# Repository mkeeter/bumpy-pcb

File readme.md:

## About

This repository contains hardware for the [bumpy](http://mattkeeter.com/projects/bumpy)
mp3 player.

## License

Copyright (c) 2014 Matthew Keeter

Permission is hereby granted, free of charge, to any person obtaining a copy of this hardware, software, and associated documentation files (the "Product"), to deal in the Product without restriction, including without limitation the rights to use, copy, modify, merge, publish, distribute, sublicense, and/or sell copies of the Product, and to permit persons to whom the Product is furnished to do so, subject to the following conditions:

The above copyright notice and this permission notice shall be included in all copies or substantial portions of the Product.

THE PRODUCT IS PROVIDED "AS IS", WITHOUT WARRANTY OF ANY KIND, EXPRESS OR IMPLIED, INCLUDING BUT NOT LIMITED TO THE WARRANTIES OF MERCHANTABILITY, FITNESS FOR A PARTICULAR PURPOSE AND NONINFRINGEMENT. IN NO EVENT SHALL THE AUTHORS OR COPYRIGHT HOLDERS BE LIABLE FOR ANY CLAIM, DAMAGES OR OTHER LIABILITY, WHETHER IN AN ACTION OF CONTRACT, TORT OR OTHERWISE, ARISING FROM, OUT OF OR IN CONNECTION WITH THE PRODUCT OR THE USE OR OTHER DEALINGS IN THE PRODUCT.

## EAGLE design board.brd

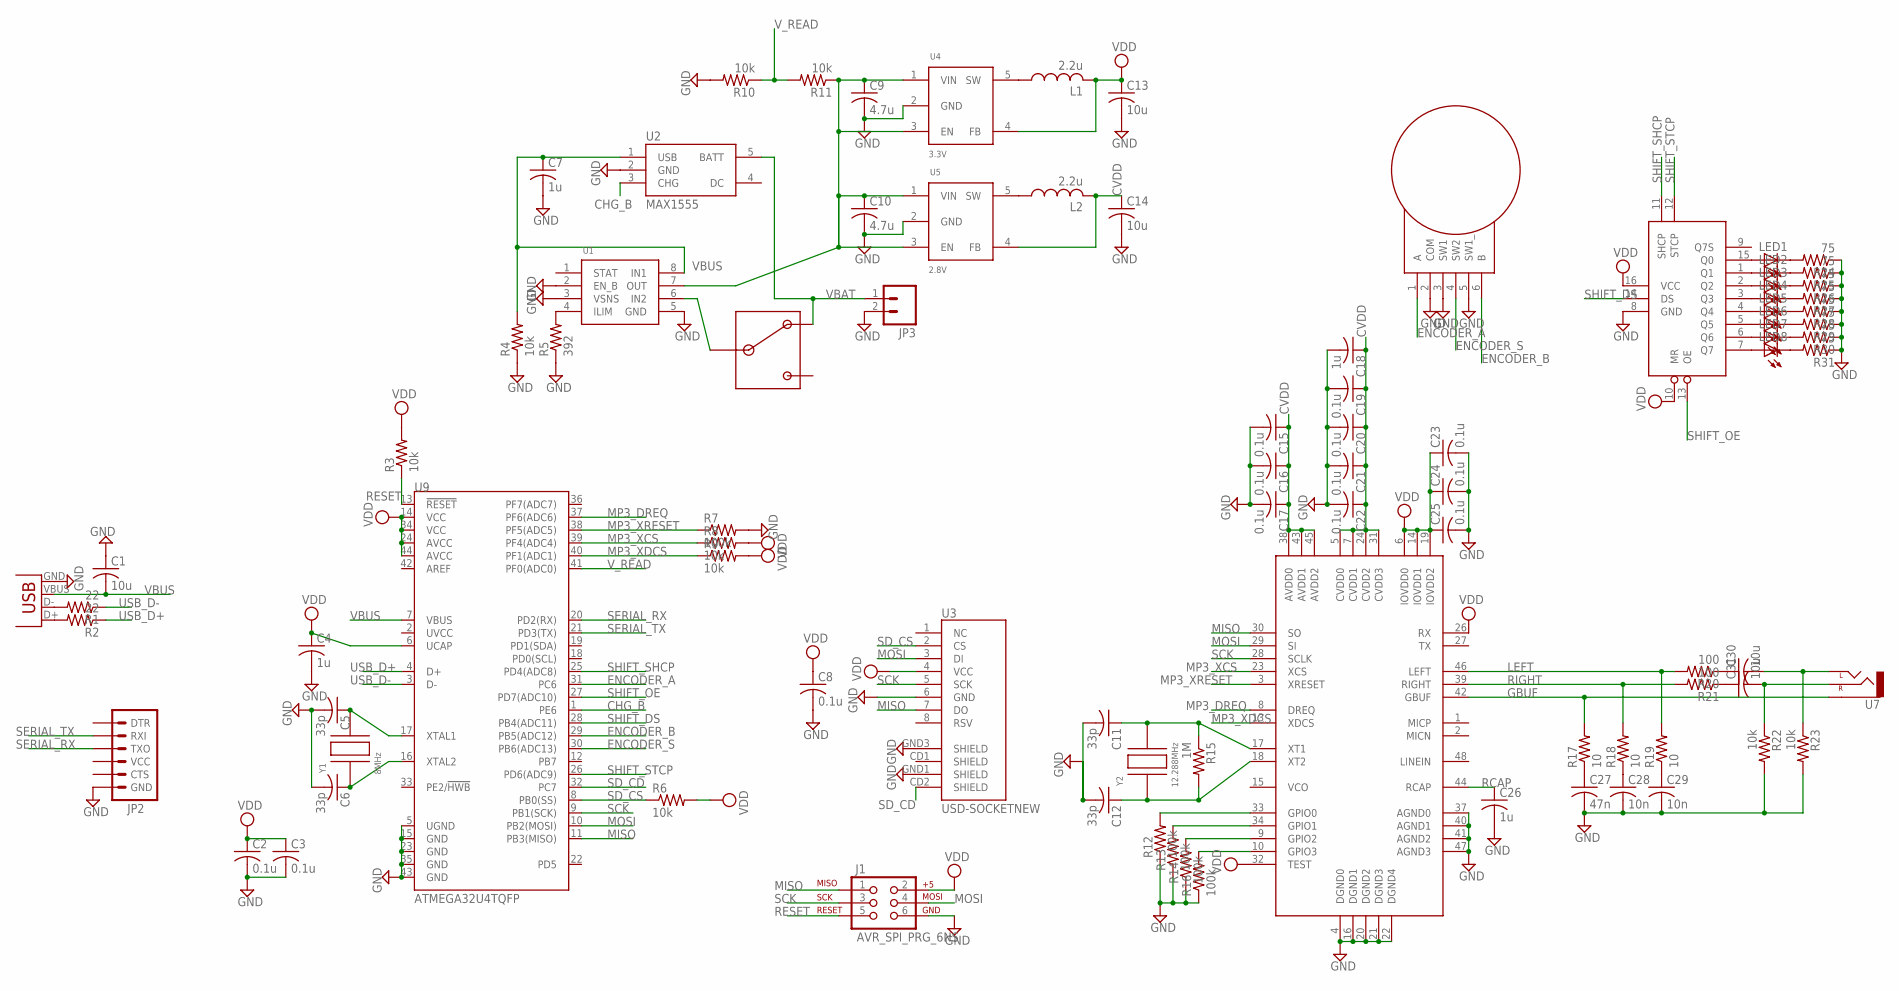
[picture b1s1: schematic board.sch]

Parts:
C1, C13, C14, C30, C31: 10u; C0603K
C2, C3, C8, C15, C16, C17, C19, C20, C21, C22, C23, C24, C25: 0.1u; C0603K
C4, C7, C18, C26: 1u; C0603K
C5, C6, C11, C12: 33p; C0603K
C9, C10: 4.7u; C0603K
C27: 47n; C0603K
C28, C29: 10n; C0603K
J1: AVR_SPI_PRG_6NS; 2X3-NS
JP1: USBSMD; USB-MINIB
JP2: ARDUINO_SERIAL_PROGRAMLOCK; 1X06_LOCK
JP3: M02PTH; 1X02
L1, L2: 2.2u; IHLP-2020CZ-11
LED1, LED2, LED3, LED4, LED5, LED6, LED7, LED8: LED1206; LED-1206
R1, R2: 22; R0603W
R3, R4, R10, R11: 10k; R0603
R5: 392; R0603
R6, R8, R9, R22, R23: 10k; R0603W
R7, R12, R13, R14, R16: 100k; R0603W
R15: 1M; R0603
R17, R18, R19: 10; R0603W
R20, R21: 100; R0603W
R24, R25, R26, R27, R28, R29, R30, R31: 75; R0603W
S1: JS102011SAQN
S2: EVQ-WKA
U1: TPS2112A; TSSOP8
U2: MAX1555; SOT23-5
U3: USD-SOCKETNEW; MICRO-SD-SOCKET-PP
U4: 3.3V; SOT23-5
U5: 2.8V; SOT23-5
U6: 74HC595; TSSOP16
U7: AUDIO-JACKSMD2; AUDIO-JACK-3.5MM-SMD
U8: VS1003; LQFP-48
U9: ATMEGA32U4TQFP; SPARKFUN-DIGITALIC_TQFP44
Y1: 8MHz; HC49/US
Y2: 12.288MHz; CSM-3X

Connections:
CHG_B: U2.3 (CHG), U9.1 (PE6)
CVDD: C14.1, C15.1, C16.1, C17.1, C18.1, C19.1, C20.1, C21.1, C22.1, L2.P$2 (2), U5.4 (FB), U8.5 (CVDD0), U8.7 (CVDD1), U8.24 (CVDD2), U8.31 (CVDD3), U8.38 (AVDD0), U8.43 (AVDD1), U8.45 (AVDD2)
ENCODER_A: S2.1 (A), U9.31 (PC6)
ENCODER_B: S2.6 (B), U9.29 (PB5(ADC12))
ENCODER_S: S2.4 (SW2), U9.30 (PB6(ADC13))
GBUF: R17.2, U7.SLEEVE, U8.42 (GBUF)
GND: C1.1, C2.2, C3.2, C4.2, C5.2, C6.2, C7.2, C8.2, C9.2, C10.2, C11.2, C12.2, C13.2, C14.2, C15.2, C16.2, C17.2, C18.2, C19.2, C20.2, C21.2, C22.2, C23.2, C24.2, C25.2, C26.2, C27.2, C28.2, C29.2, J1.6, JP1.GND, JP2.6 (GND), JP3.2, R4.1, R5.1, R7.2, R10.2, R12.1, R13.1, R14.1, R16.1, R22.2, R23.2, R24.1, R25.1, R26.1, R27.1, R28.1, R29.1, R30.1, R31.1, S2.2 (COM), S2.3 (SW1), S2.5 (SW1_), U1.2 (EN_B), U1.3 (VSNS), U1.5 (GND), U2.2 (GND), U3.6 (GND), U3.GND1 (SHIELD), U3.GND3 (SHIELD), U4.2 (GND), U5.2 (GND), U6.8 (GND), U8.4 (DGND0), U8.16 (DGND1), U8.20 (DGND2), U8.21 (DGND3), U8.22 (DGND4), U8.37 (AGND0), U8.40 (AGND1), U8.41 (AGND2), U8.47 (AGND3), U9.5 (UGND), U9.15 (GND), U9.23 (GND), U9.35 (GND), U9.43 (GND)
GPIO0: R12.2, U8.33 (GPIO0)
GPIO1: R13.2, U8.34 (GPIO1)
GPIO2: R14.2, U8.9 (GPIO2)
GPIO3: R16.2, U8.10 (GPIO3)
LEFT: R19.2, R20.2, U8.46 (LEFT)
MISO: J1.1, U3.7 (DO), U8.30 (SO), U9.11 (PB3(MISO))
MOSI: J1.4, U3.3 (DI), U8.29 (SI), U9.10 (PB2(MOSI))
MP3_DREQ: U8.8 (DREQ), U9.37 (PF6(ADC6))
MP3_XCS: R8.1, U8.23 (XCS), U9.39 (PF4(ADC4))
MP3_XDCS: R9.1, U8.13 (XDCS), U9.40 (PF1(ADC1))
MP3_XRESET: R7.1, U8.3 (XRESET), U9.38 (PF5(ADC5))
unnamed: JP1.D-, R1.2
unnamed: C5.1, U9.17 (XTAL1), Y1.P$2
unnamed: C27.1, R17.1
unnamed: C28.1, R18.1
unnamed: C29.1, R19.1
unnamed: JP1.D+, R2.2
unnamed: C12.1, R15.2, U8.18 (XT2), Y2.P$1
unnamed: C11.1, R15.1, U8.17 (XT1), Y2.P$2
unnamed: C31.1, R21.1
unnamed: C30.1, R20.1
unnamed: C31.2, R22.1, U7.RING (RIGHT)
unnamed: C30.2, R23.1, U7.TIP (LEFT)
unnamed: C6.1, U9.16 (XTAL2), Y1.P$1
unnamed: R5.2, U1.4 (ILIM)
unnamed: C9.1, C10.1, R11.1, U1.7 (OUT), U4.1 (VIN), U4.3 (EN), U5.1 (VIN), U5.3 (EN)
unnamed: LED8.A, U6.7 (Q7)
unnamed: LED7.A, U6.6 (Q6)
unnamed: LED6.A, U6.5 (Q5)
unnamed: LED5.A, U6.4 (Q4)
unnamed: LED4.A, U6.3 (Q3)
unnamed: LED3.A, U6.2 (Q2)
unnamed: LED2.A, U6.1 (Q1)
unnamed: LED1.A, U6.15 (Q0)
unnamed: LED1.C, R24.2
unnamed: LED2.C, R25.2
unnamed: LED3.C, R26.2
unnamed: LED4.C, R27.2
unnamed: LED5.C, R28.2
unnamed: LED6.C, R29.2
unnamed: LED7.C, R30.2
unnamed: LED8.C, R31.2
unnamed: L1.P$1 (1), U4.5 (SW)
unnamed: L2.P$1 (1), U5.5 (SW)
unnamed: S1.P$2 (2), U1.6 (IN2)
RCAP: C26.1, U8.44 (RCAP)
RESET: J1.5, R3.1, U9.13 (!RESET)
RIGHT: R18.2, R21.2, U8.39 (RIGHT)
SCK: J1.3, U3.5 (SCK), U8.28 (SCLK), U9.9 (PB1(SCK))
SD_CD: U3.CD2 (SHIELD), U9.32 (PC7)
SD_CS: R6.1, U3.2 (CS), U9.8 (PB0(SS))
SERIAL_RX: JP2.3 (TXO), U9.20 (PD2(RX))
SERIAL_TX: JP2.2 (RXI), U9.21 (PD3(TX))
SHIFT_DS: U6.14 (DS), U9.28 (PB4(ADC11))
SHIFT_OE: U6.13 (OE), U9.27 (PD7(ADC10))
SHIFT_SHCP: U6.11 (SHCP), U9.25 (PD4(ADC8))
SHIFT_STCP: U6.12 (STCP), U9.26 (PD6(ADC9))
USB_D+: R2.1, U9.4 (D+)
USB_D-: R1.1, U9.3 (D-)
VBAT: JP3.1, S1.P$3 (3), U2.5 (BATT)
VBUS: C1.2, C7.1, JP1.VBUS, R4.2, U1.8 (IN1), U2.1 (USB), U9.7 (VBUS)
VDD: C2.1, C3.1, C4.1, C8.1, C13.1, C23.1, C24.1, C25.1, J1.2, L1.P$2 (2), R3.2, R6.2, R8.2, R9.2, U3.4 (VCC), U4.4 (FB), U6.10 (MR), U6.16 (VCC), U8.6 (IOVDD0), U8.14 (IOVDD1), U8.19 (IOVDD2), U8.26 (RX), U8.32 (TEST), U9.6 (UCAP), U9.14 (VCC), U9.24 (AVCC), U9.34 (VCC), U9.44 (AVCC)
V_READ: R10.1, R11.2, U9.41 (PF0(ADC0))

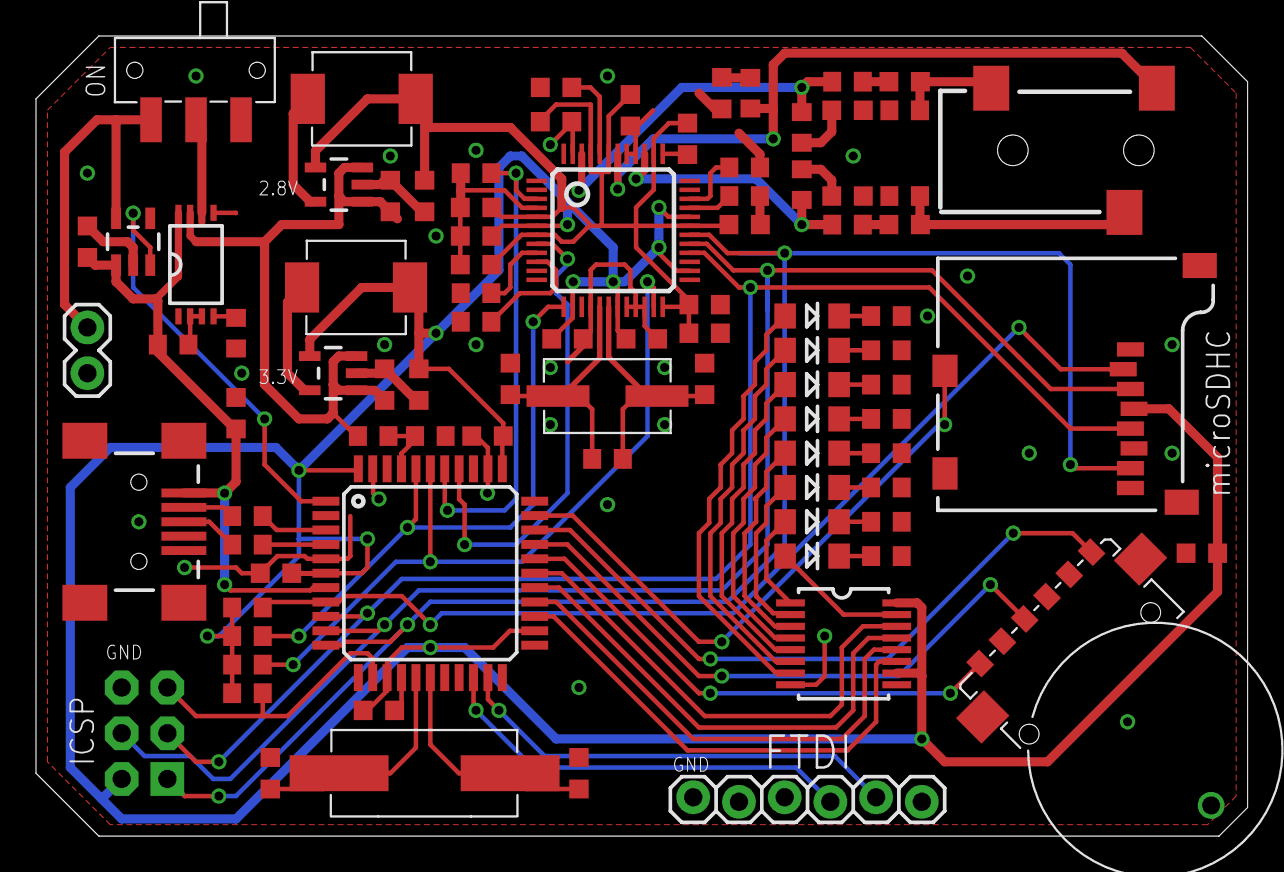
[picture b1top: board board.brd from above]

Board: 2 copper layers, 67.3 x 44.4 mm, 89 parts (0 on the bottom side), 70 nets.

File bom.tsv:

Name	Vendor	Part number	Count	Identifier
12.288 MHz crystal	Digikey	XC1771CT-ND	1	Y2
8 MHz crystal	Digikey	XC1271CT-ND	1	Y1
Power switcher	Digikey	296-34595-5-ND	1	U1
Encoder wheel	Digikey	P13381SCT-ND	1	S2
8-bit shift register	Digikey	568-2263-1-ND	1	U6
Green LED (1206)	Digikey	160-1169-1-ND	8	LED1-8
2.8V buck regulator	Digikey	LM3671MF-2.8/NOPBCT-ND	1	U5
3.3V buck regulator	Digikey	LM3671MF-3.3/NOPBCT-ND	1	U4
2.2uH inductor	Digikey	541-1236-1-ND	2	L1, L2
Slide switch	Digikey	401-1999-1-ND	1	S1
MicroSD holder	Digikey	732-3819-1-ND	1	U3
USB mini plug	Digikey	ED2992CT-ND	1	JP1
Audio jack	Digikey	CP-3523SJCT-ND	1	U7
6-pin FTDI header	Digikey	A106757-ND	1	JP2
6-pin SPI header	Digikey	A106478-ND	1	J1
Atmega32u4	Digikey	ATMEGA32U4-AURCT-ND	1	U9
Max1555 charger	Digikey	MAX1555EZK+TCT-ND	1	U2
				
10 Ohm 0603 resistor	Digikey	P10GCT-ND	3	R17, R18, R19
22 Ohm 0603 resistor	Digikey	P22GCT-ND	2	R1, R2
75 Ohm 0603 resistor	Digikey	P75GCT-ND	8	R24-31
100 Ohm 0603 resistor	Digikey	P100GCT-ND	2	R20, R21
392 Ohm 0603 resistor	Digikey	P392HCT-ND	1	R5
10 Kohm 0603 resistor	Digikey	P10KGCT-ND	7	R3, R4, R10, R11
100 Kohm 0603 resistor	Digikey	P100KGCT-ND	5	R7, R12,R13, R14, R16
1 MOhm 0603 resistor	Digikey	P1.0MGCT-ND	1	R15
				
33 pF 0603 capacitor	Digikey	1276-2267-1-ND	4	C5, C6, C11, C12
10 nF 0603 capacitor	Digikey	445-1311-1-ND	2	C28, C29
47 nF 0603 capacitor	Digikey	445-1313-1-ND	1	C27
0.1 uF 0603 capacitor	Digikey	445-1314-1-ND	12	C2, C3, C8, C15, C16, C17, C19, C20, C21, C22, C23, C24, C25
1 uF 0603 capacitor	Digikey	445-1322-1-ND	4	C4, C7, C18, C26
4.7 uF 0603 capacitor	Digikey	445-5178-1-ND	2	C9, C10
10 uF 0603 capacitor	Digikey	445-4112-1-ND	5	C1, C13, C14, C30, C31
				
1000 mAh Lithium battery	Sparkfun	PRT-00339 	1	JP3
MP3 codec	Sparkfun	COM-09398	1	U8

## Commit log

2013-12-05 Here comes the files
2013-12-05 Fixed scroll wheel package (lousy datasheet!)
2013-12-05 Board shrink
2013-12-05 Not sure why I shorted VDD with an open-drain output to ground.
2013-12-05 Connected XTest on vs1063 to VDD
2013-12-05 Switched to 0603W packages for audio path resistors
2013-12-05 Shifted VS1003 over a bit
2013-12-05 Finished layout
2013-12-05 Added pull-ups to mp3 cs lines
2013-12-05 Moved shift register over a bit
2013-12-05 Renumbered parts
2013-12-05 Switched to smaller uC and VS1003 chip
2013-12-05 Beginning to switch to atmega32u2
2013-12-05 PCB trace cleaning
2013-12-05 Removed battery outline
2013-12-05 Tightened resistor spacing
2013-12-05 Switched audio plug to 3-pin version and added OE connection
2013-12-05 Renamed stuff
2013-12-05 More board cleanup
2013-12-05 Moved voltage labels
2013-12-05 Moved SPI header to fit battery
2013-12-05 Moved battery plug and SD capacitor
2013-12-05 Debugging rev2 board
2013-12-05 Misaligned top layer
2013-12-05 Switching back to atmega32u4
2013-12-05 0.1" shrink on y axis
2013-12-05 Capacitor value fixes and obsessive pcb trace cleanup
2013-12-05 Fixed rear silkscreen
2013-12-05 Rough connections are made.
2013-12-05 More connections
2013-12-07 A bit more beveling on corners
2013-12-07 Ignore temporary board and schematic files
2013-12-07 Make wheel stick out more
2013-12-07 Added battery sense, updated revision, and centered LEDs
2013-12-07 Trace cleanup
2013-12-07 A bit more space between audio jack and sdhc
2013-12-08 Move switch to be flush with board
2013-12-08 More trace cleanup
2013-12-08 Removed battery cutout on milling layer
2013-12-09 More trace cleaning
2013-12-09 Last bit of cleanup
2013-12-09 Moved revision number to bottom
2013-12-09 More gap between LEDs and shift register
2014-03-18 Why wasn't UCAP connected to VDD?
2014-04-24 Adding bom
2014-04-27 Atmega32u2 -> u4
2014-04-27 Adding license and readme
2014-06-06 Bump revision
2014-06-06 ...and bump release date
2014-06-11 Re-ordered components, added identifiers to BOM, and fixed power switching
2014-06-11 Bump version number
2014-06-11 Adding assembly diagram
2014-06-11 Fix weird unicode that snuck into the BOM
2014-06-20 Added missing resistors to bom

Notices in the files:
parts and their libraries:
SparkFun-Connectors: Licensing: CC v3.0 Share-Alike You are welcome to use this library for commercial purposes.
